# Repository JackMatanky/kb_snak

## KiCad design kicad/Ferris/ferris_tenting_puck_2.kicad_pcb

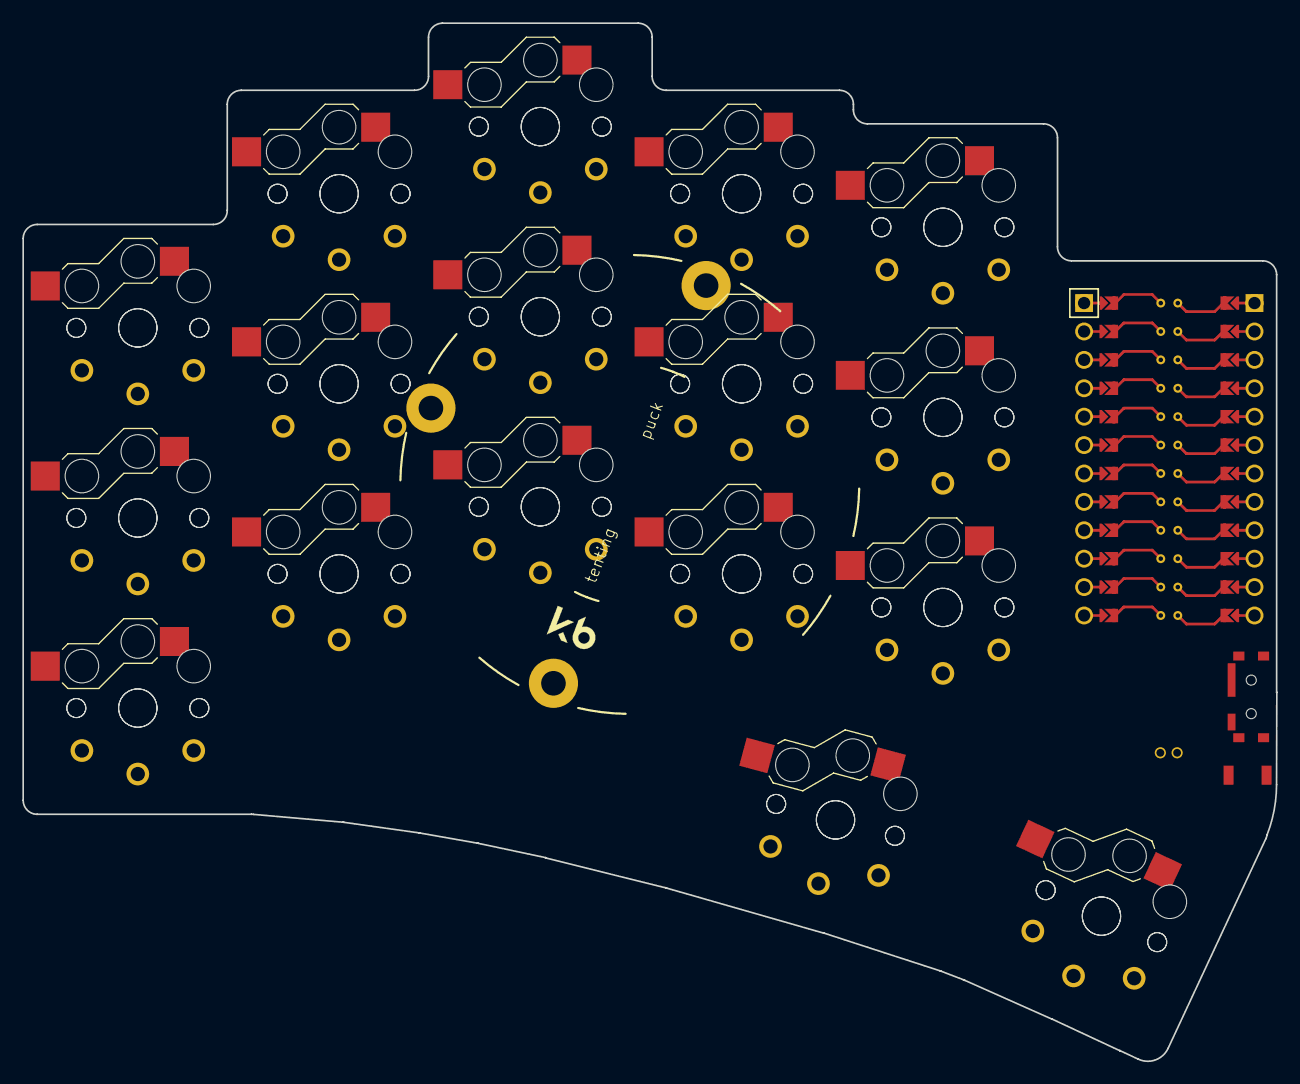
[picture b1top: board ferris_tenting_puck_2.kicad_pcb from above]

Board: 2 copper layers, 112.1 x 92.8 mm, 36 parts (0 on the bottom side), 18 nets, no tracks yet.

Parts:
MCU1: ProMicro
S1, S2, S3, S4, S5, S6, S7, S8, S9, S10, S11, S12, S13, S14, S15, S16, S17, S18, S19, S20, S21, S22, S23, S24, S25, S26, S27, S28, S29, S30, S31, S32, S33, S34: PG1350
_1: Tenting Puck

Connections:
GND: MCU1.2, MCU1.21, MCU1.22, S1.2, S2.2, S3.2, S4.2, S5.2, S6.2, S7.2, S8.2, S9.2, S10.2, S11.2, S12.2, S13.2, S14.2, S15.2, S16.2, S17.2, S18.2, S19.2, S20.2, S21.2, S22.2, S23.2, S24.2, S25.2, S26.2, S27.2, S28.2, S29.2, S30.2, S31.2, S32.2, S33.2, S34.2
P0: MCU1.23, S9.1, S26.1
P1: MCU1.24, S15.1, S32.1
P2: MCU1.20, S3.1, S20.1
P3: MCU1.19, S14.1, S31.1
P4: MCU1.18, S8.1, S25.1
P5: MCU1.17, S2.1, S19.1
P6: MCU1.16, S13.1, S30.1
P7: MCU1.15, S7.1, S24.1
P8: MCU1.14, S1.1, S18.1
P9: MCU1.13, S16.1, S33.1
P10: MCU1.12, S17.1, S34.1
P14: MCU1.10, S4.1, S21.1
P15: MCU1.9, S10.1, S27.1
P18: MCU1.8, S5.1, S22.1
P19: MCU1.7, S11.1, S28.1
P20: MCU1.6, S6.1, S23.1
P21: MCU1.5, S12.1, S29.1

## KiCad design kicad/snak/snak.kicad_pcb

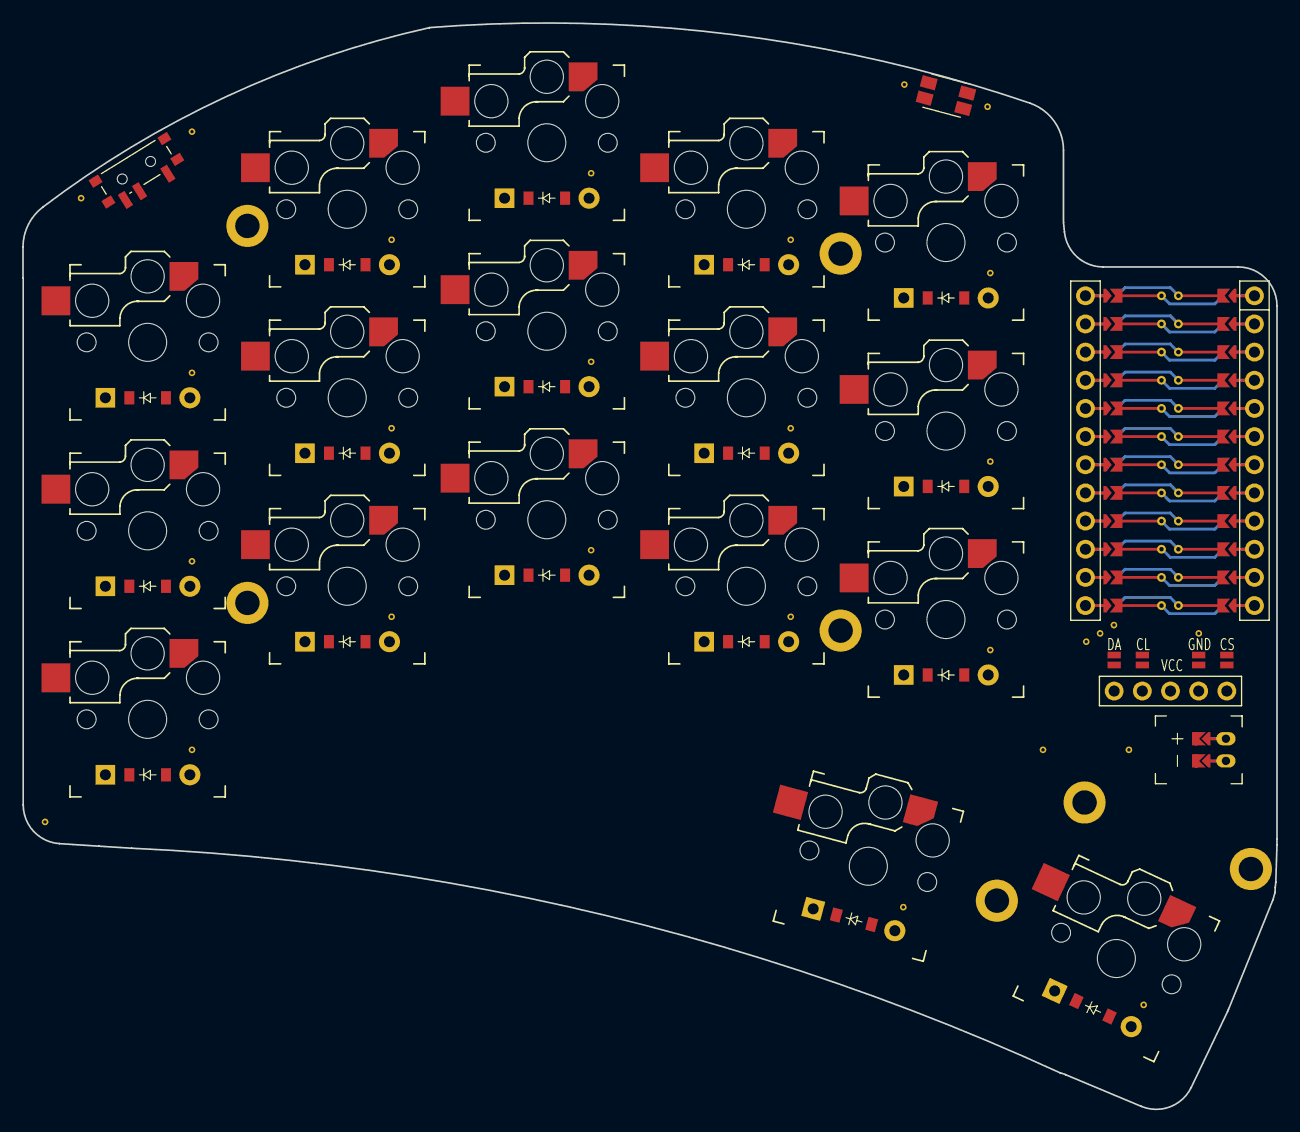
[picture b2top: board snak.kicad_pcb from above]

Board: 2 copper layers, 113.1 x 98.0 mm, 46 parts (0 on the bottom side), 40 nets.

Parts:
D1, D2, D3, D4, D5, D6, D7, D8, D9, D10, D11, D12, D13, D14, D15, D16, D17: ComboDiode
DISP1: nice!view
H1, H2, H3, H4, H5, H6, H7: mounting_hole
JST1: JST_PH_S2B-PH-K
MCU1: nice_nano
S1, S2, S3, S4, S5, S6, S7, S8, S9, S10, S11, S12, S13, S14, S15, S16, S17: PG1350
SW1: sw_reset_side
SW2: power_switch

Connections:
DISP1_1: DISP1.1, DISP1.10, DISP1.23
DISP1_2: DISP1.2, DISP1.11, DISP1.22
DISP1_4: DISP1.4, DISP1.12, DISP1.21
DISP1_5: DISP1.5, DISP1.13, DISP1.20
GND: DISP1.16, DISP1.26, JST1.1, MCU1.103, MCU1.104, MCU1.123, SW1.1
JST1_1: JST1.11, JST1.21, JST1.31
JST1_2: JST1.12, JST1.22, JST1.32
P0: MCU1.102, S4.1, S5.1, S6.1
P1: MCU1.101, S1.1, S2.1, S3.1
P2: MCU1.105, S7.1, S8.1, S9.1
P3: MCU1.106, S10.1, S11.1, S12.1, S16.1
P4: MCU1.107, S13.1, S14.1, S15.1, S17.1
P5: DISP1.14, DISP1.24, MCU1.108
P6: DISP1.15, DISP1.25, MCU1.109
P7: DISP1.17, DISP1.27, MCU1.110
P10: D16.1, D17.1, MCU1.113
P14: D2.1, D5.1, D8.1, D11.1, D14.1, MCU1.115
P15: D3.1, D6.1, D9.1, D12.1, D15.1, MCU1.116
P16: D1.1, D4.1, D7.1, D10.1, D13.1, MCU1.114
RAW: MCU1.124, SW2.3, SW2.6
RST: MCU1.122, SW1.2
VCC: DISP1.3, MCU1.121
in_home: D17.2, S17.2
index_bot: D10.2, S10.2
index_mid: D11.2, S11.2
index_top: D12.2, S12.2
inner_bot: D13.2, S13.2
inner_mid: D14.2, S14.2
inner_top: D15.2, S15.2
middle_bot: D7.2, S7.2
middle_mid: D8.2, S8.2
middle_top: D9.2, S9.2
out_home: D16.2, S16.2
pinky_bot: D1.2, S1.2
pinky_mid: D2.2, S2.2
pinky_top: D3.2, S3.2
pos: JST1.2, SW2.2, SW2.5
ring_bot: D4.2, S4.2
ring_mid: D5.2, S5.2
ring_top: D6.2, S6.2
